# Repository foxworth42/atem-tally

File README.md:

# atem-tally
Yet another Arduino based ATEM tally light system.  This system is self-contained and talks to the ATEM directly.  The on camera lights are neo pixels driven over RS485 to allow for long cable runs.  The cabling between the cameras is done using ethernet cables for simplicity of wiring so we can send power + data to the remote lights.  The tally controller will also have a 20x4 LCD display for showing system status.  An XBee can also be added for supporting wireless remote tally lights.

# Still a work-in-progress

Everything here is still a work in process at the moment.  

Arduino code makes use of [Skaarhoj's Open Engineering arduino libraries](https://github.com/kasperskaarhoj/SKAARHOJ-Open-Engineering/tree/master/ArduinoLibs) for communicating with the Black Magic ATEM video switcher

Why roll something myself?  Cost, and it's an excuse to learn some C and do some PCB design.

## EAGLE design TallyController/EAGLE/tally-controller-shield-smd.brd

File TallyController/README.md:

Arduino based tally controller using the Arduino Mega w/ Ethernet.

Configuration of the tally controller is done via serial connection.  To configure send the following:

|Setting|Command|Note|
|---|---|---|
|Controller's IP|`Ix.x.x.x`|Replace x's with the controller's IP address|
|Controller's Netmask|`Nx.x.x.x`|Replace the x's with the controller's netmask|
|ATEM's IP|`Ax.x.x.x`|Replace the x's with the ATEM's IP address|
|Remote Camera #|`Rx`|Replace the x's with the camera # the wireless tally light is attached to|

Sample build of ATEM tally controller built in a parts organizer for portability for on-location use at conventions.

# BOM:

## Controller Board:

For `tally-controller-shield-smd.brd`

|Component|Quantity|Notes|Link|
|---|---|---|---|
|Controller Shield PCB|1|Can have board fabbed anywhere.|[Link](https://oshpark.com/shared_projects/vglxha97)|
|Freetronics EtherMEGA|1|Arduino Mega + Ethernet bundle.  I do not recommend using the Mega ETH from RobotDyn.|[Link](https://www.freetronics.com.au/products/ethermega-arduino-mega-2560-compatible-with-onboard-ethernet)|
|SN75174N RS485 Quad Line Driver|3| |[Link](https://www.mouser.com/ProductDetail/595-SN75174N)|
|LM2596 DC/DC buck converters|2|I used 1 for the main 5v for the project, and the other just for powering the Ethermega|[Link](https://www.amazon.com/dp/B06XZ1DKF2/ref=cm_sw_em_r_mt_dp_U_vQXREb0CJX45Z)|
|Molex 22-23-2021 2-pin header|4| |[Link](https://www.mouser.com/ProductDetail/538-22-23-2021)|
|Molex 22-23-2031 3-pin header|3| |[Link](https://www.mouser.com/ProductDetail/538-22-23-2031)|
|Molex 22-23-2041 4-pin header|2| |[Link](https://www.mouser.com/ProductDetail/538-22-23-2041)|
|Molex 22-23-2081 8-pin header|3| |[Link](https://www.mouser.com/ProductDetail/538-22-23-2081)|
|470ohm 0805 SMD resistor|1| | |
|10kohm 0805 SMD resistor|1| | |
|4.7kohm 0805 SMD resistor|1| | |
|120ohm 0805 SMD resistor|12| | |
|0.1uf 0805 SMD ceramic capacitor|3| | |
|10kohm potentiometer|2| |[Link](https://www.mouser.com/ProductDetail/858-P231-QC15BR10K)|
|1kohm potentiometer|1| | |
|Potentiometer knob|3| |[Red](https://www.mouser.com/ProductDetail/450-3021), [Green](https://www.mouser.com/ProductDetail/450-3024), [Blue](https://www.mouser.com/ProductDetail/450-3023), [Yellow](https://www.mouser.com/ProductDetail/450-3022)
|SPST Toggle Swithch|1| | |
|Mean Well RS-25-12 Power Supply|1| |[Link](https://www.mouser.com/ProductDetail/709-RS25-12)|
|Sparkfun XBee regulated breakout|1|Optional|[Link](https://www.mouser.com/ProductDetail/474-WRL-11373)|
|XBee Pro Transciever|1|Optional|[Link](https://www.mouser.com/ProductDetail/888-XB3-24Z8ST)|
|Dome atenna for Xbee|1|Optional|[Link](https://www.mouser.com/ProductDetail/712-ANT-DB1-WRT-RPS)|
|20x4 LCD i2c Display|1|Can be had cheap off ebay| |

## Camera output board:

For `RJ45 4ch Outout.brd`

Quantities noted here are for each output board.  Multiply as needed for multiple boards.

|Component|Quantity|Notes|Link|
|---|---|---|---|
|Output PCB|1|Oshpark minimum order is 3|[Link](https://oshpark.com/shared_projects/SH81yZph)|
|Amphenol RJHSE-5380-04|1|4-port RJ45 module|[Link](https://www.mouser.com/ProductDetail/523-RJHSE-5380-04)|
|Molex 22-23-2021 2-pin header|4|Only needed for CAM#DATA1 headers.  CAM#DATA2 is unused currently.|[Link](https://www.mouser.com/ProductDetail/538-22-23-2021)|

## Power distribution

For `Output Power Distro.brd`

Small board for distributing the 5v power to the controller shield, camera output boards

|Component|Quantity|Notes|Link|
|---|---|---|---|
|Power Distro PCB|1|Oshpark minimum order is 3|[Link](https://oshpark.com/shared_projects/CbdMb8Fg)|
|Molex 22-23-2021 2-pin header|6|Only needed for CAM#DATA1 headers.  CAM#DATA2 is unused currently.|[Link](https://www.mouser.com/ProductDetail/538-22-23-2021)|

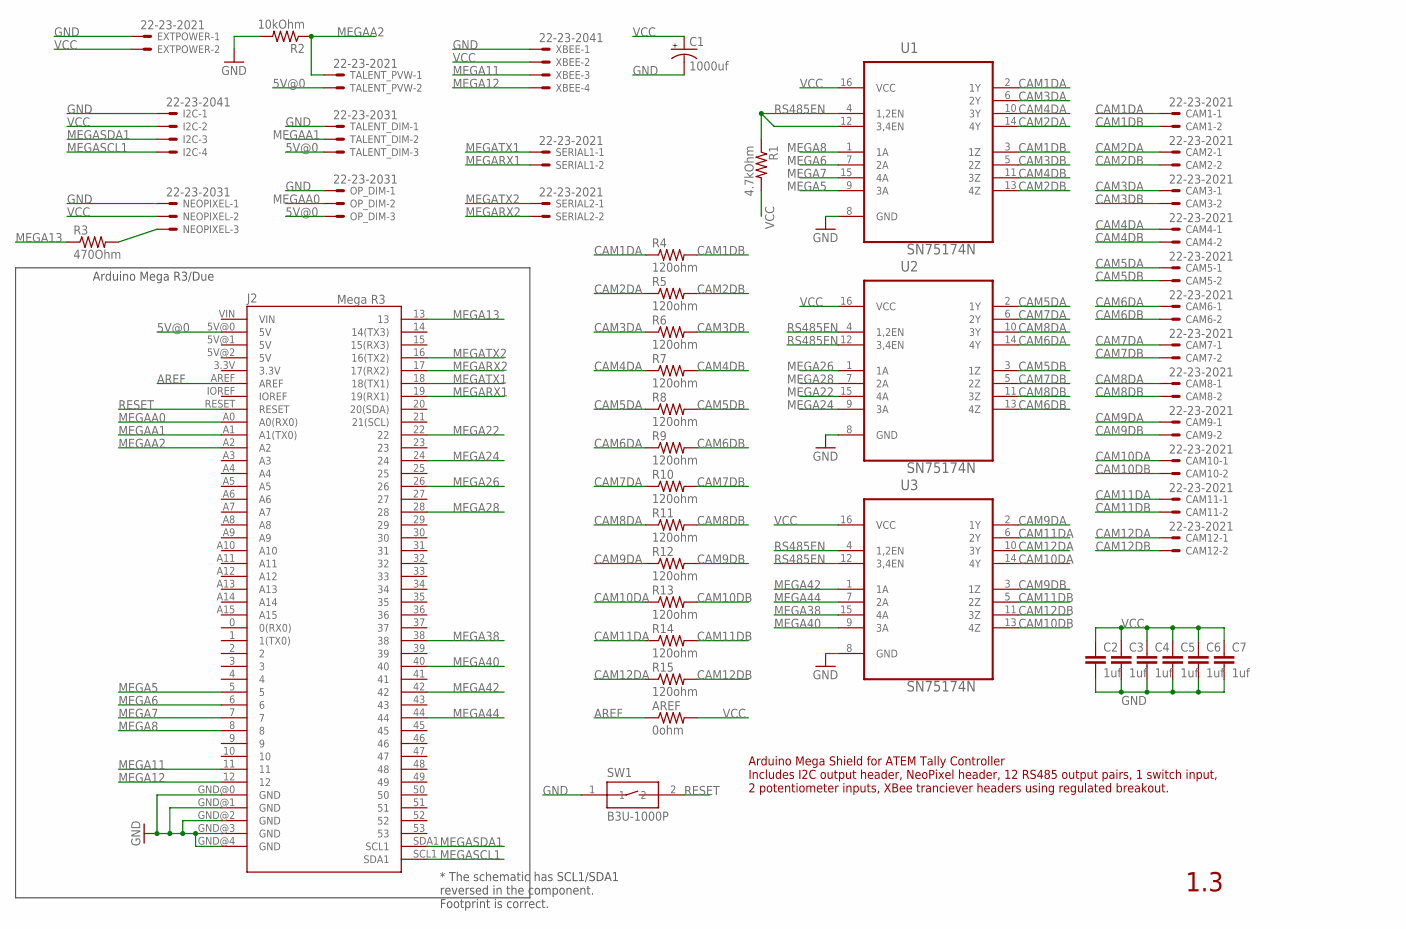
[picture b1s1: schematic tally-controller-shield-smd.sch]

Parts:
AREF: 0ohm; 0204V
C1: 1000uf; CPOL-RADIAL-5MM-10MM
C2, C3, C4, C5, C6, C7: 1uf; RESC0805_N
CAM1, CAM2, CAM3, CAM4, CAM5, CAM6, CAM7, CAM8, CAM9, CAM10, CAM11, CAM12: 22-23-2021
EXTPOWER: 22-23-2021
I2C: 22-23-2041
J2: Mega R3; ARDUINO_MEGA
NEOPIXEL: 22-23-2031
OP_DIM: 22-23-2031
R1: 4.7kOhm; R0805
R2: 10kOhm; R0805
R3: 470Ohm; R0805
R4, R5, R6, R7, R8, R9, R10, R11, R12, R13, R14, R15: 120ohm; R0805
SERIAL1, SERIAL2: 22-23-2021
SW1: B3U-1000P
TALENT_DIM: 22-23-2031
TALENT_PVW: 22-23-2021
U1, U2, U3: SN75174N; DIP254P762X508-16
XBEE: 22-23-2041

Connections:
5V@0: J2.5V@0 (5V), OP_DIM.3, TALENT_DIM.3, TALENT_PVW.2
AREF: AREF.1, J2.AREF
CAM1DA: CAM1.1, R4.1, U1.2 (1Y)
CAM1DB: CAM1.2, R4.2, U1.3 (1Z)
CAM2DA: CAM2.1, R5.1, U1.14 (4Y)
CAM2DB: CAM2.2, R5.2, U1.13 (4Z)
CAM3DA: CAM3.1, R6.1, U1.6 (2Y)
CAM3DB: CAM3.2, R6.2, U1.5 (2Z)
CAM4DA: CAM4.1, R7.1, U1.10 (3Y)
CAM4DB: CAM4.2, R7.2, U1.11 (3Z)
CAM5DA: CAM5.1, R8.1, U2.2 (1Y)
CAM5DB: CAM5.2, R8.2, U2.3 (1Z)
CAM6DA: CAM6.1, R9.1, U2.14 (4Y)
CAM6DB: CAM6.2, R9.2, U2.13 (4Z)
CAM7DA: CAM7.1, R10.1, U2.6 (2Y)
CAM7DB: CAM7.2, R10.2, U2.5 (2Z)
CAM8DA: CAM8.1, R11.1, U2.10 (3Y)
CAM8DB: CAM8.2, R11.2, U2.11 (3Z)
CAM9DA: CAM9.1, R12.1, U3.2 (1Y)
CAM9DB: CAM9.2, R12.2, U3.3 (1Z)
CAM10DA: CAM10.1, R13.1, U3.14 (4Y)
CAM10DB: CAM10.2, R13.2, U3.13 (4Z)
CAM11DA: CAM11.1, R14.1, U3.6 (2Y)
CAM11DB: CAM11.2, R14.2, U3.5 (2Z)
CAM12DA: CAM12.1, R15.1, U3.10 (3Y)
CAM12DB: CAM12.2, R15.2, U3.11 (3Z)
GND: C1.-, C2.2, C3.2, C4.2, C5.2, C6.2, C7.2, EXTPOWER.1, I2C.1, J2.GND@0 (GND), J2.GND@1 (GND), J2.GND@2 (GND), J2.GND@3 (GND), J2.GND@4 (GND), NEOPIXEL.1, OP_DIM.1, R2.2, SW1.1, TALENT_DIM.1, U1.8 (GND), U2.8 (GND), U3.8 (GND), XBEE.1
MEGA5: J2.5, U1.9 (3A)
MEGA6: J2.6, U1.7 (2A)
MEGA7: J2.7, U1.15 (4A)
MEGA8: J2.8, U1.1 (1A)
MEGA11: J2.11, XBEE.3
MEGA12: J2.12, XBEE.4
MEGA13: J2.13, R3.1
MEGA22: J2.22, U2.15 (4A)
MEGA24: J2.24, U2.9 (3A)
MEGA26: J2.26, U2.1 (1A)
MEGA28: J2.28, U2.7 (2A)
MEGA38: J2.38, U3.15 (4A)
MEGA40: J2.40, U3.9 (3A)
MEGA42: J2.42, U3.1 (1A)
MEGA44: J2.44, U3.7 (2A)
MEGAA0: J2.A0 (A0(RX0)), OP_DIM.2
MEGAA1: J2.A1 (A1(TX0)), TALENT_DIM.2
MEGAA2: J2.A2, R2.1, TALENT_PVW.1
MEGARX1: J2.19 (19(RX1)), SERIAL1.2
MEGARX2: J2.17 (17(RX2)), SERIAL2.2
MEGASCL1: I2C.4, J2.SCL1 (SDA1)
MEGASDA1: I2C.3, J2.SDA1 (SCL1)
MEGATX1: J2.18 (18(TX1)), SERIAL1.1
MEGATX2: J2.16 (16(TX2)), SERIAL2.1
NEOPIXELDATA: NEOPIXEL.3, R3.2
RESET: J2.RESET, SW1.2
RS485EN: R1.1, U1.4 (1,2EN), U1.12 (3,4EN), U2.4 (1,2EN), U2.12 (3,4EN), U3.4 (1,2EN), U3.12 (3,4EN)
VCC: AREF.2, C1.+, C2.1, C3.1, C4.1, C5.1, C6.1, C7.1, EXTPOWER.2, I2C.2, NEOPIXEL.2, R1.2, U1.16 (VCC), U2.16 (VCC), U3.16 (VCC), XBEE.2

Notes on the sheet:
Arduino Mega R3/Due
Arduino Mega Shield for ATEM Tally Controller Includes I2C output header, NeoPixel header, 12 RS485 output pairs, 1 switch input, 2 potentiometer inputs, XBee tranciever headers using regulated breakout.
1.3
* The schematic has SCL1/SDA1 reversed in the component. Footprint is correct.

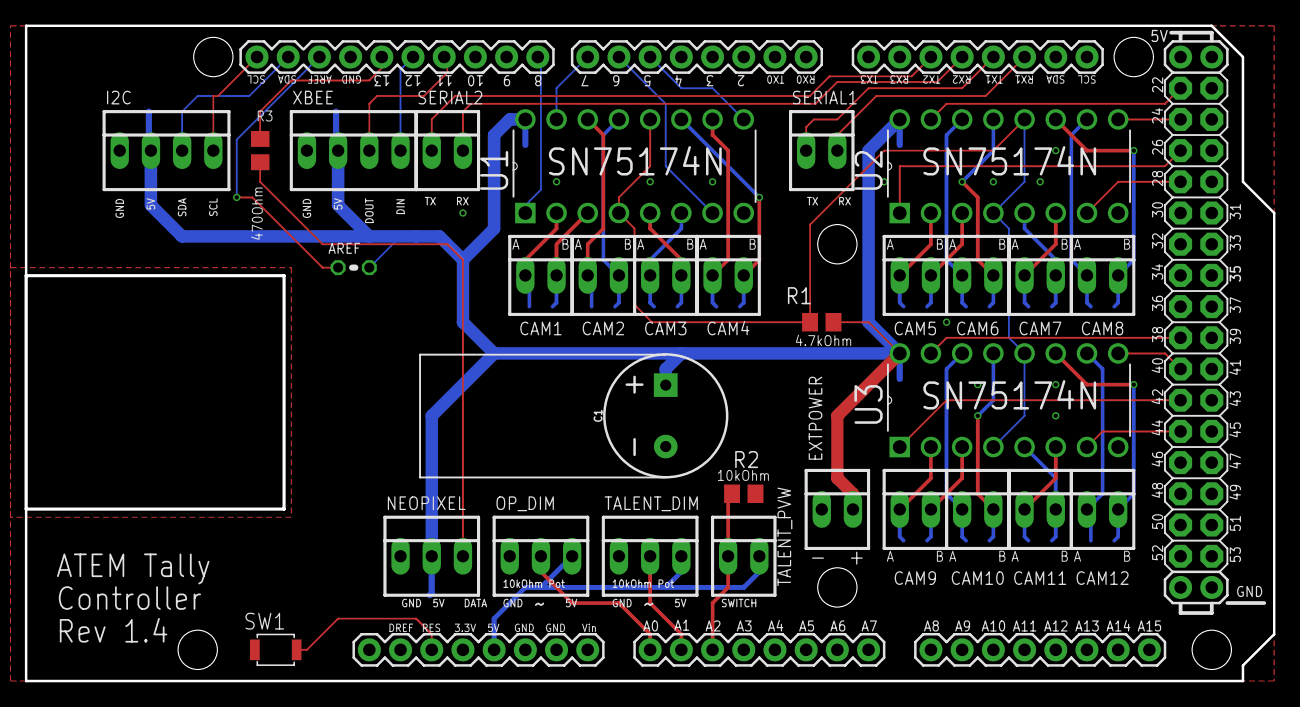
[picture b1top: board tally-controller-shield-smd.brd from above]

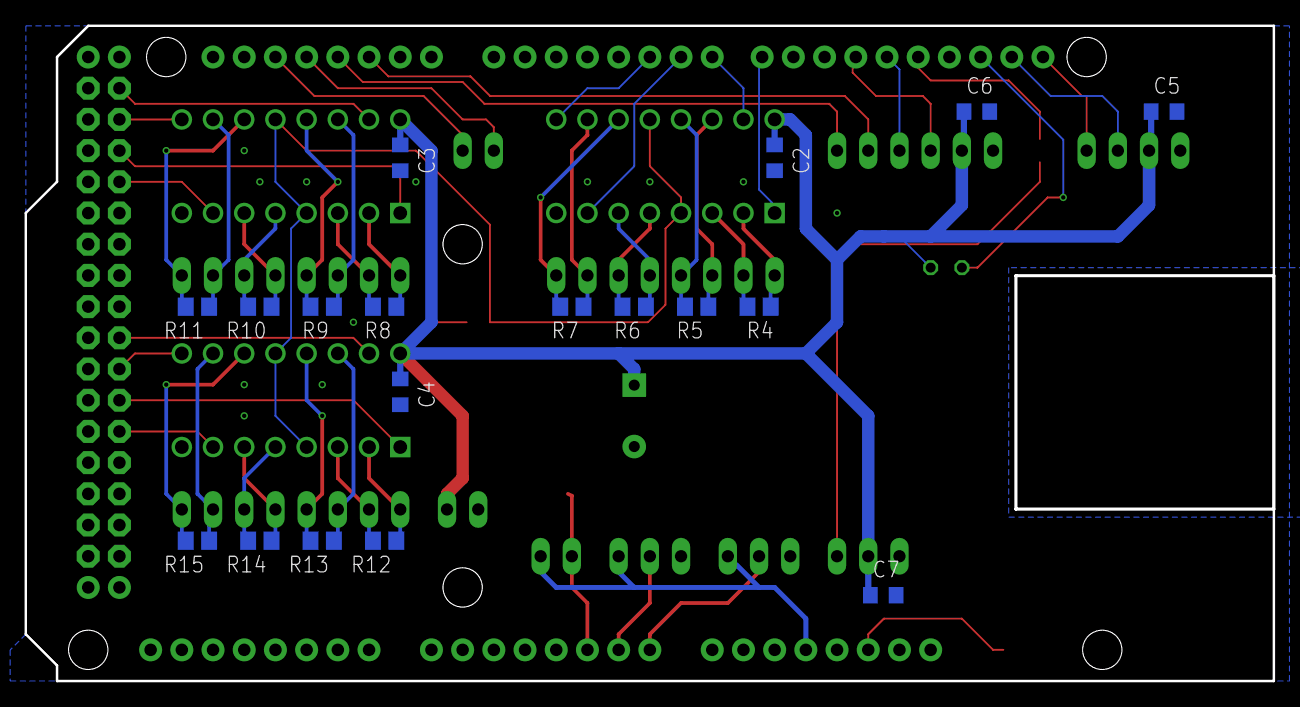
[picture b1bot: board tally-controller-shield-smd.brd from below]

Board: 2 copper layers, 101.6 x 53.3 mm, 49 parts (18 on the bottom side), 55 nets.

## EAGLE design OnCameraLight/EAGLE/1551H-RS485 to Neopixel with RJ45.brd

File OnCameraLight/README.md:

RS485 receiver to Neopixel adapter for on-camera light.

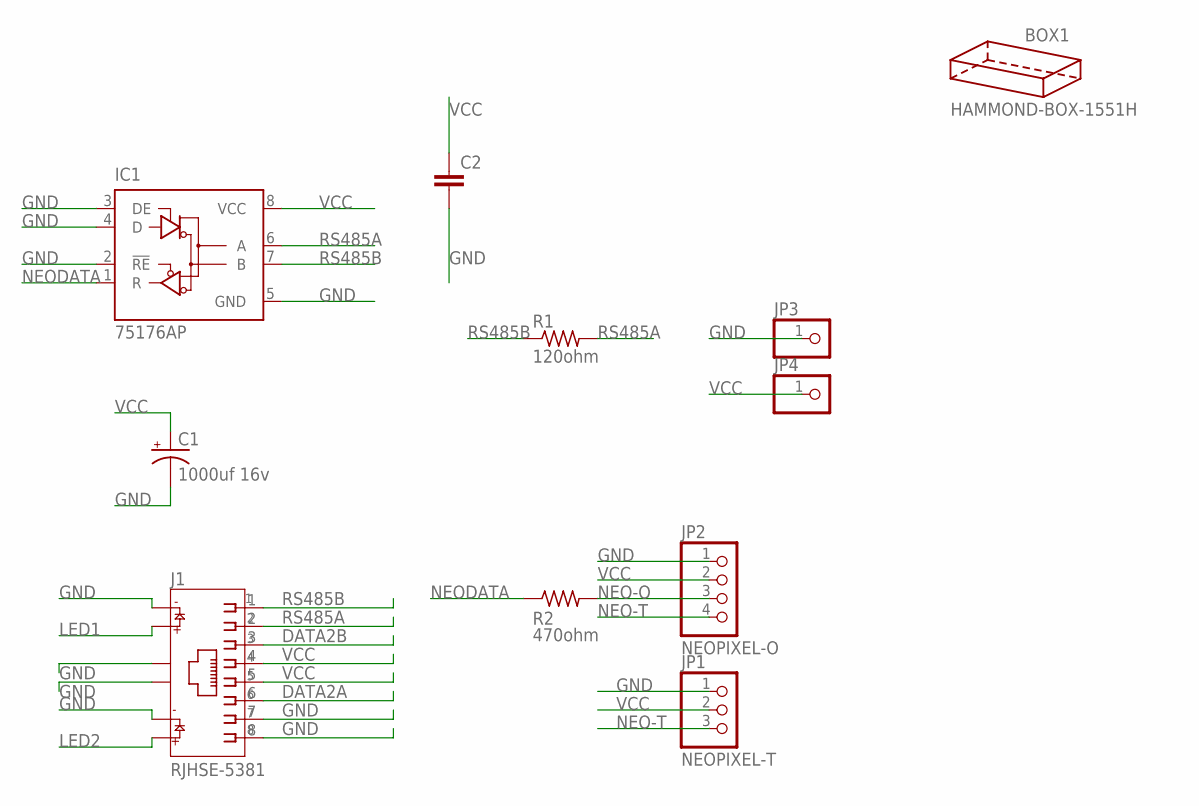
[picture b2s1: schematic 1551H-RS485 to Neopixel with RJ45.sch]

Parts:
BOX1: HAMMOND-BOX-1551H; 1551H
C1: 1000uf 16v; CPOL-RADIAL-5MM-10MM
C2: CAPACITOR_0805_N; RESC0805_N
IC1: 75176AP; DIL08
J1: RJHSE-5381; AMPHENOL_RJHSE-5381
JP1: NEOPIXEL-T; 1X03
JP2: NEOPIXEL-O; 1X04
JP3, JP4: PINHD-1X1; 1X01
R1: 120ohm; R0805
R2: 470ohm; R0805

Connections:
DATA2A: J1.6
DATA2B: J1.3
GND: C1.-, C2.2, IC1.2 (!RE), IC1.3 (DE), IC1.4 (D), IC1.5 (GND), J1.7, J1.8, J1.9, J1.11, J1.S1, J1.S2, JP1.1, JP2.1, JP3.1
LED1: J1.10
LED2: J1.12
NEO-O: JP2.3, R2.2
NEO-T: JP1.3, JP2.4
NEODATA: IC1.1 (R), R2.1
RS485A: IC1.6 (A), J1.2, R1.2
RS485B: IC1.7 (B), J1.1, R1.1
VCC: C1.+, C2.1, IC1.8 (VCC), J1.4, J1.5, JP1.2, JP2.2, JP4.1

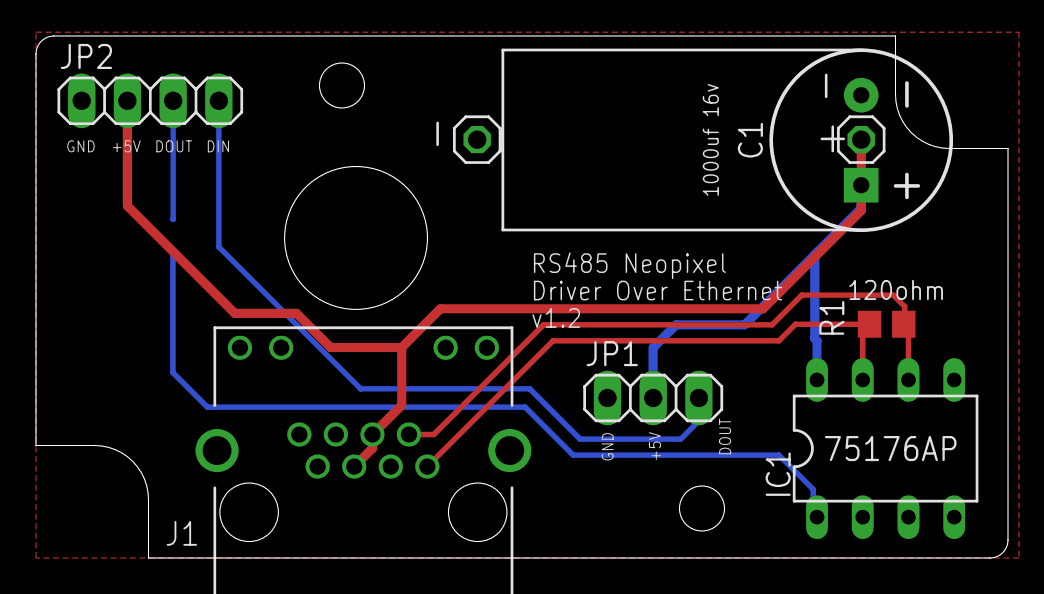
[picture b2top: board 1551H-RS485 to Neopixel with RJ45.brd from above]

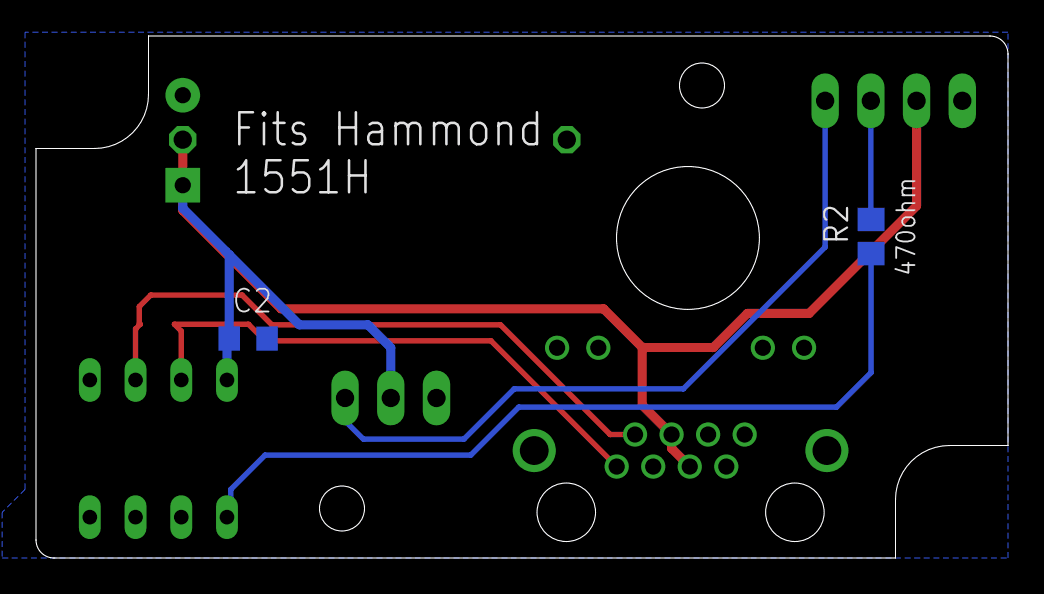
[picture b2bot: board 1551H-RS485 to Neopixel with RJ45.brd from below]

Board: 2 copper layers, 54.0 x 29.0 mm, 11 parts (2 on the bottom side), 7 nets.

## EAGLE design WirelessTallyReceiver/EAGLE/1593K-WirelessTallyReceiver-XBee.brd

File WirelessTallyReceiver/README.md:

XBee + Arduino Mini Pro based tally receiver.  Uses the same Neopixel LEDs as the wired lights, but wireless.

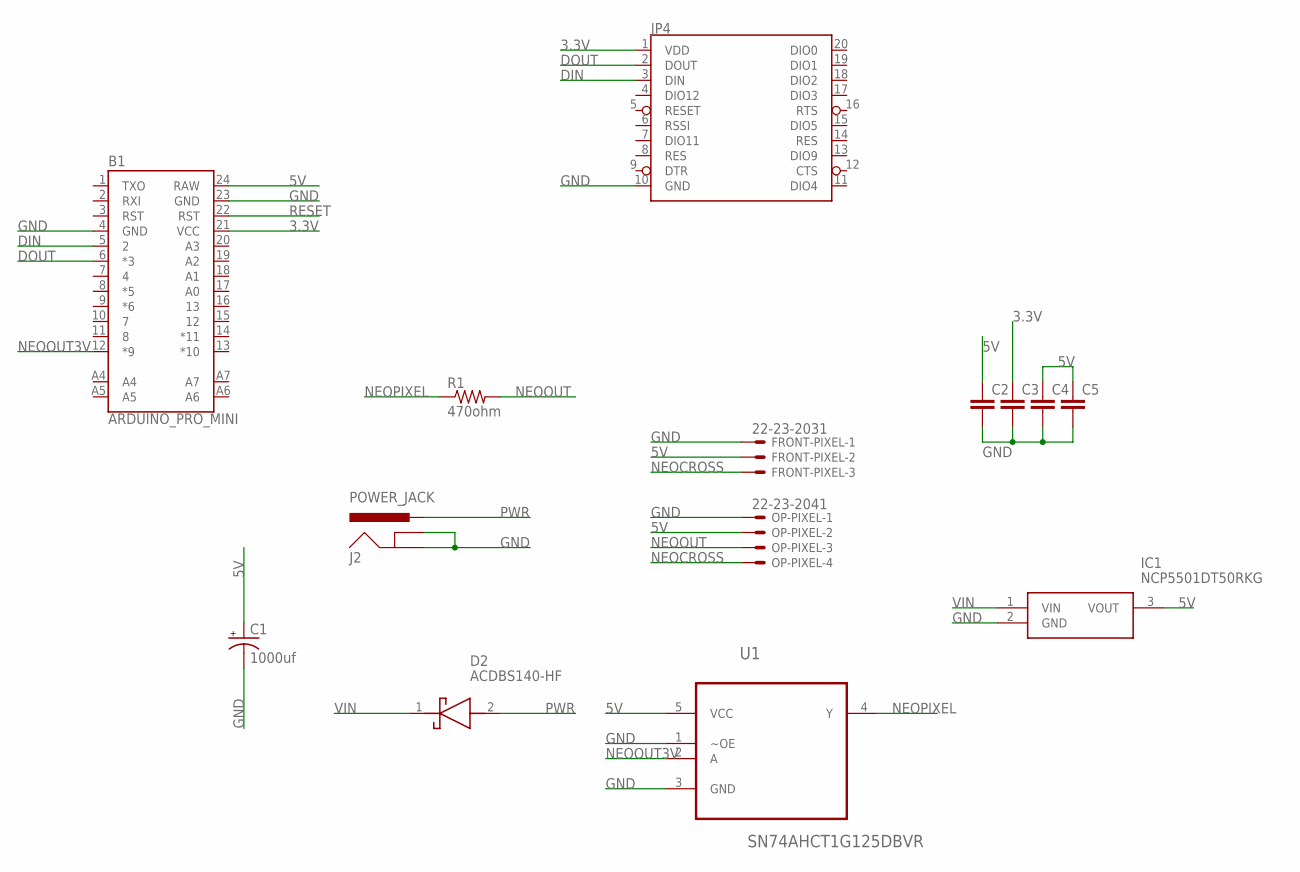
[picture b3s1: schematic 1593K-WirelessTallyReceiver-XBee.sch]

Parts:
B1: ARDUINO_PRO_MINI
C1: 1000uf; CPOL-RADIAL-5MM-10MM
C2, C3, C4, C5: CAPACITOR_0805_N; RESC0805_N
D2: ACDBS140-HF; DIOM2013X100N
FRONT-PIXEL: 22-23-2031
IC1: NCP5501DT50RKG
J2: POWER_JACK; POWER_JACK_PTH
JP4: XBEESILK; XBEE-SILK
OP-PIXEL: 22-23-2041
R1: 470ohm; R0805
U1: SN74AHCT1G125DBVR; SOT95P280X145-5N

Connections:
3.3V: B1.21 (VCC), C3.1, JP4.1 (VDD)
5V: B1.24 (RAW), C1.+, C2.1, C4.1, C5.1, FRONT-PIXEL.2, IC1.3 (VOUT), OP-PIXEL.2, U1.5 (VCC)
DIN: B1.5 (2), JP4.3 (DIN)
DOUT: B1.6 (*3), JP4.2 (DOUT)
GND: B1.4 (GND), B1.23 (GND), C1.-, C2.2, C3.2, C4.2, C5.2, FRONT-PIXEL.1, IC1.2 (GND), J2.GND, J2.GNDBREAK, JP4.10 (GND), OP-PIXEL.1, U1.1 (~OE), U1.3 (GND)
NEOCROSS: FRONT-PIXEL.3, OP-PIXEL.4
NEOOUT: OP-PIXEL.3, R1.2
NEOOUT3V: B1.12 (*9), U1.2 (A)
NEOPIXEL: R1.1, U1.4 (Y)
PWR: D2.2 (A), J2.PWR
RESET: B1.22 (RST)
VIN: D2.1 (K), IC1.1 (VIN)

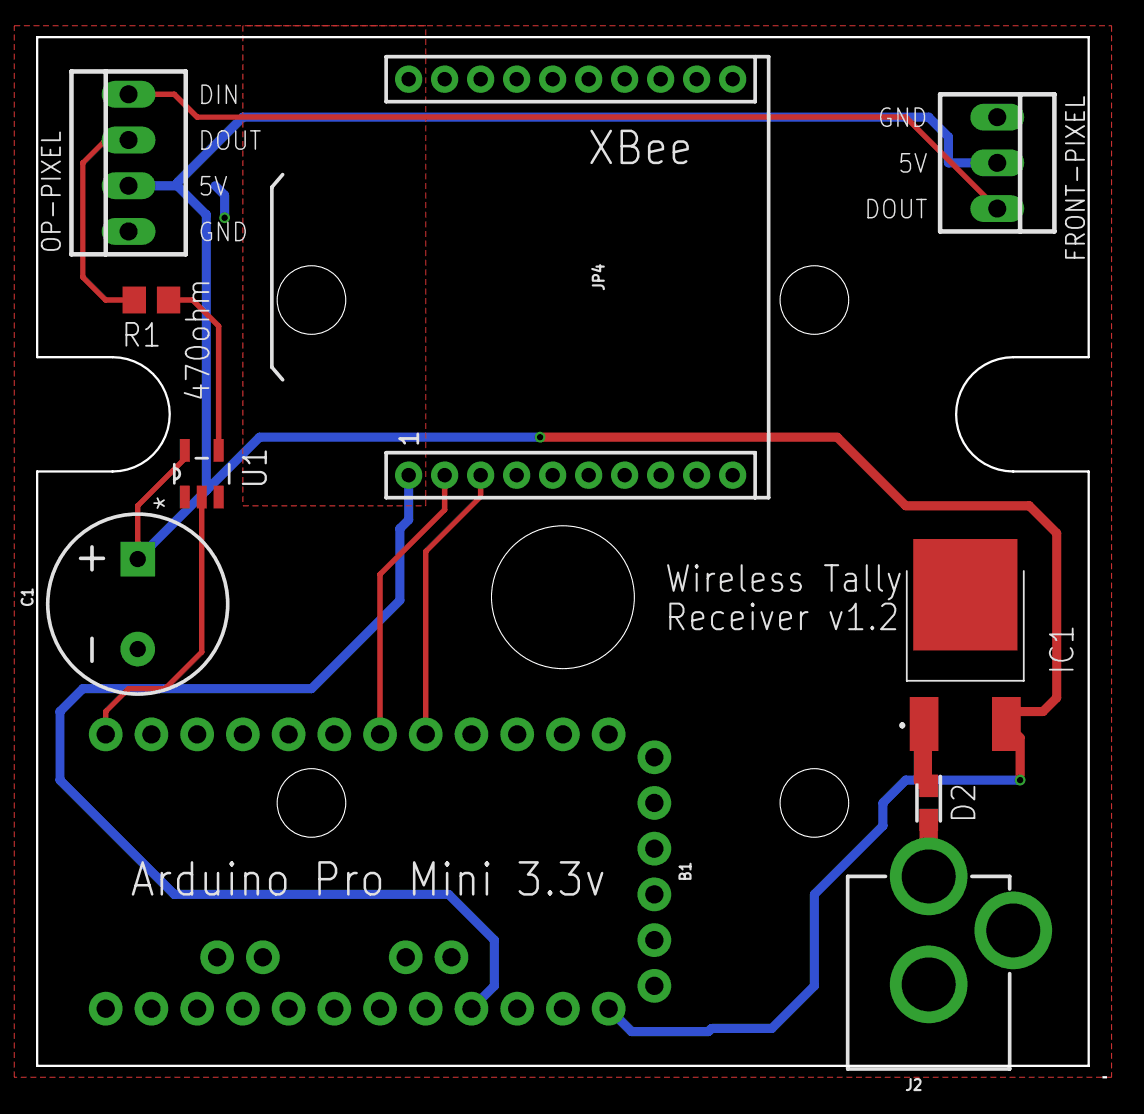
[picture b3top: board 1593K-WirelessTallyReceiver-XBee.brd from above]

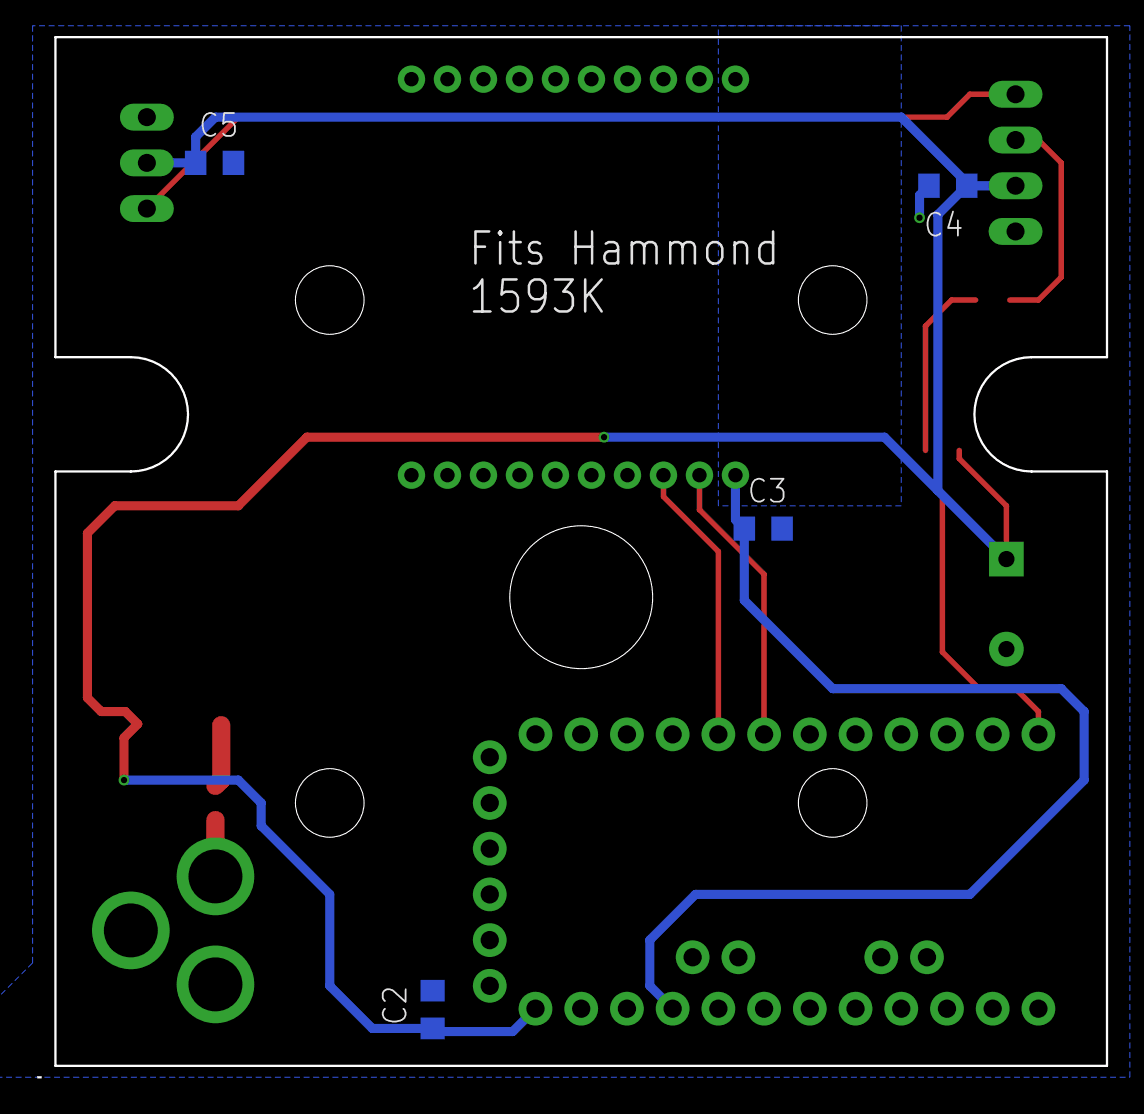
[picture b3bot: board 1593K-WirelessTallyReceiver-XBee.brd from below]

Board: 2 copper layers, 59.4 x 57.8 mm, 15 parts (4 on the bottom side), 11 nets.

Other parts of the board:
U$1: 1593K

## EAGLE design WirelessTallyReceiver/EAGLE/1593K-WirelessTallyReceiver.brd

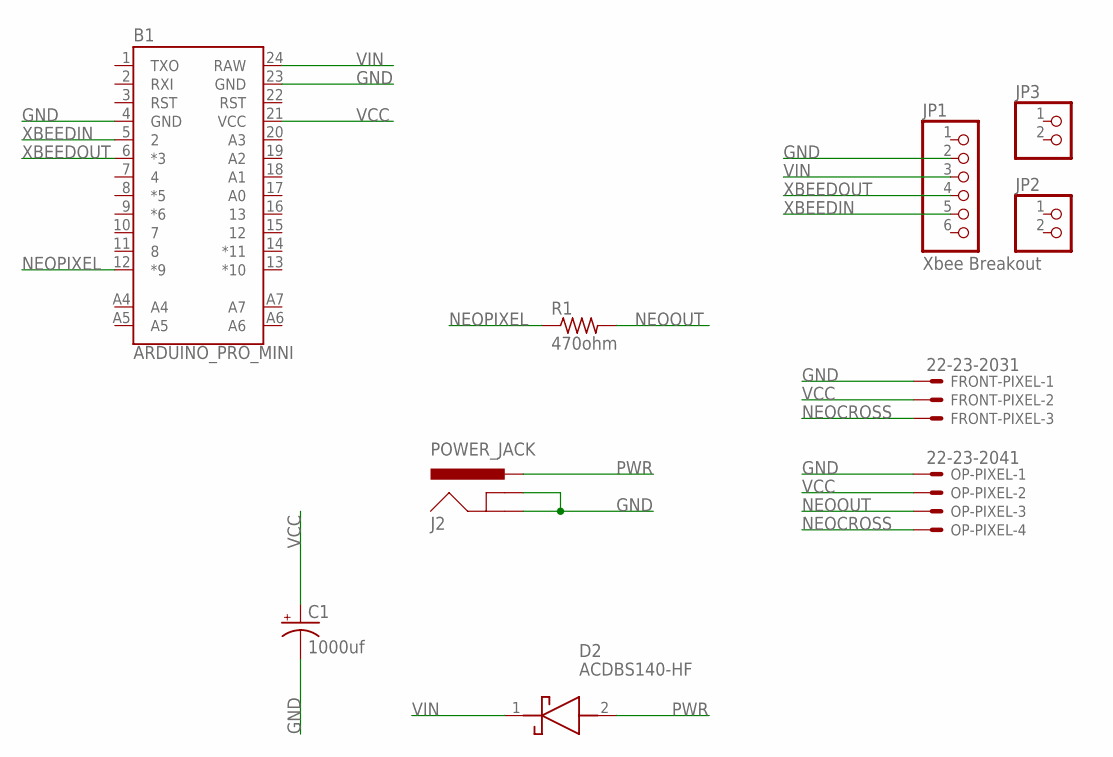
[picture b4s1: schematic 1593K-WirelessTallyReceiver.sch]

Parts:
B1: ARDUINO_PRO_MINI
C1: 1000uf; CPOL-RADIAL-5MM-10MM
D2: ACDBS140-HF; DIOM2013X100N
FRONT-PIXEL: 22-23-2031
J2: POWER_JACK; POWER_JACK_PTH
JP1: Xbee Breakout; 1X06
JP2, JP3: PINHD-1X2; 1X02
OP-PIXEL: 22-23-2041
R1: 470ohm; R0805

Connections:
GND: B1.4 (GND), B1.23 (GND), C1.-, FRONT-PIXEL.1, J2.GND, J2.GNDBREAK, JP1.2, OP-PIXEL.1
NEOCROSS: FRONT-PIXEL.3, OP-PIXEL.4
NEOOUT: OP-PIXEL.3, R1.2
NEOPIXEL: B1.12 (*9), R1.1
PWR: D2.2 (A), J2.PWR
VCC: B1.21 (VCC), C1.+, FRONT-PIXEL.2, OP-PIXEL.2
VIN: B1.24 (RAW), D2.1 (K), JP1.3
XBEEDIN: B1.5 (2), JP1.5
XBEEDOUT: B1.6 (*3), JP1.4

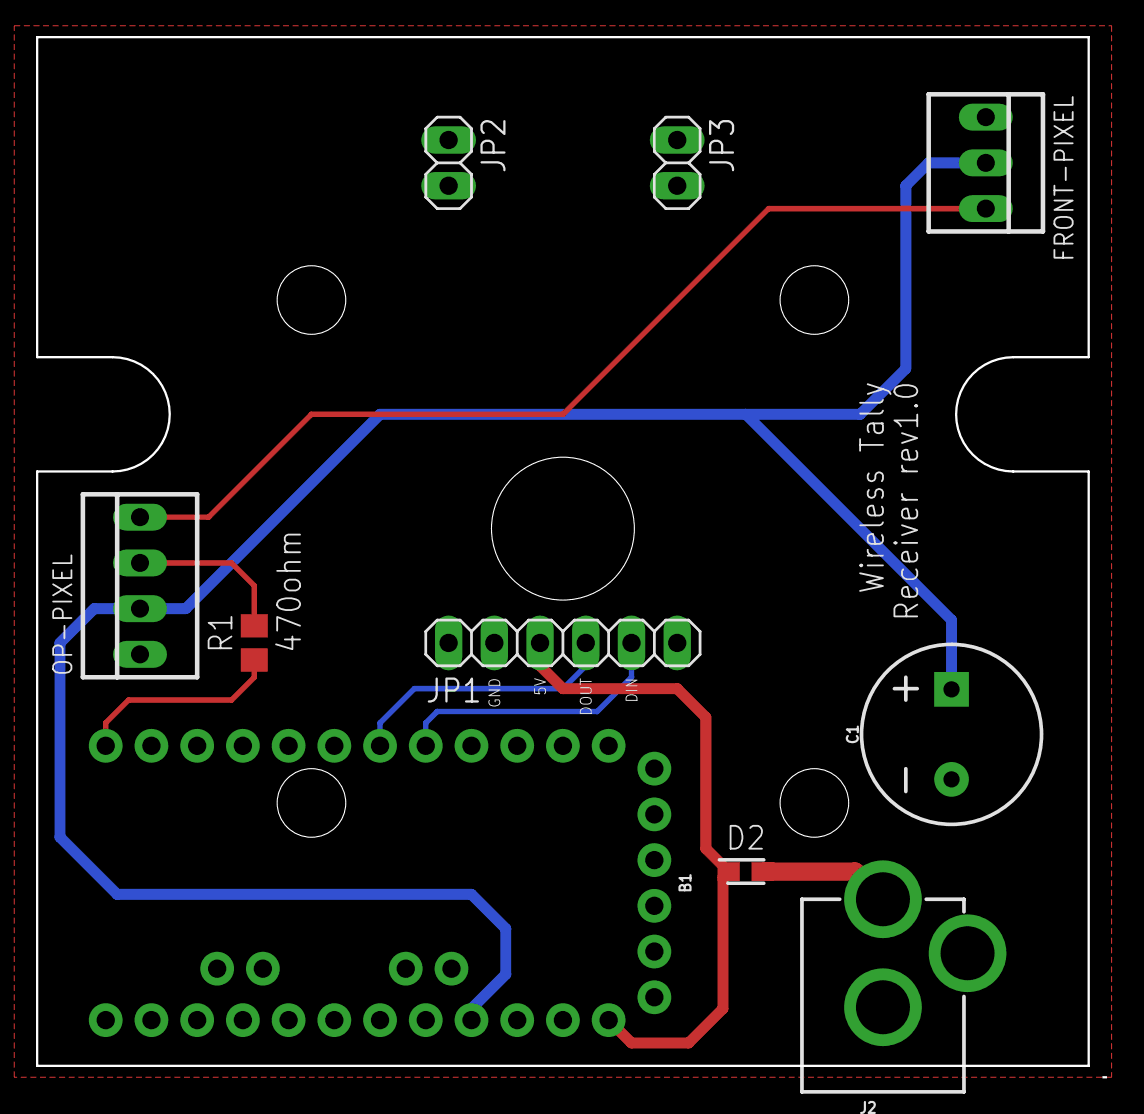
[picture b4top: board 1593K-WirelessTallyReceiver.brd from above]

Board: 2 copper layers, 59.4 x 57.8 mm, 11 parts (0 on the bottom side), 9 nets.

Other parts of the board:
U$1: 1593K

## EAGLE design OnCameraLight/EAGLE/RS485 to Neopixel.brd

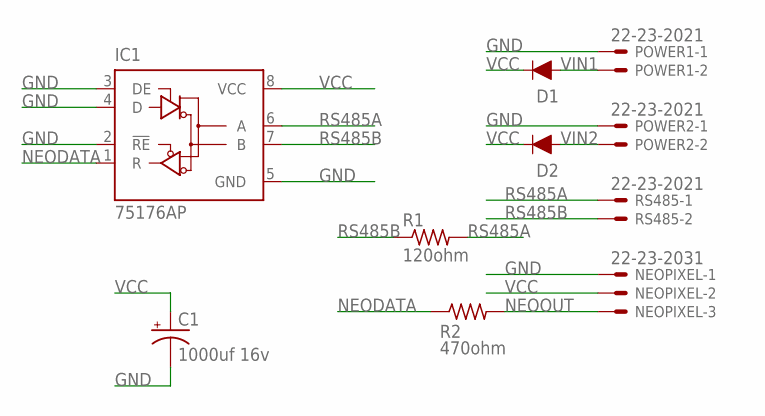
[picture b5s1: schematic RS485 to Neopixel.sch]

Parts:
C1: 1000uf 16v; CPOL-RADIAL-5MM-10MM
D1, D2: 1A/50V/1.1V; DIODE-1N4001
IC1: 75176AP; DIL08
NEOPIXEL: 22-23-2031
POWER1, POWER2: 22-23-2021
R1: 120ohm; 0207/10
R2: 470ohm; 0207/10
RS485: 22-23-2021

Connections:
GND: C1.-, IC1.2 (!RE), IC1.3 (DE), IC1.4 (D), IC1.5 (GND), NEOPIXEL.1, POWER1.1, POWER2.1
NEODATA: IC1.1 (R), R2.1
NEOOUT: NEOPIXEL.3, R2.2
RS485A: IC1.6 (A), R1.2, RS485.1
RS485B: IC1.7 (B), R1.1, RS485.2
VCC: C1.+, D1.C, D2.C, IC1.8 (VCC), NEOPIXEL.2
VIN1: D1.A, POWER1.2
VIN2: D2.A, POWER2.2

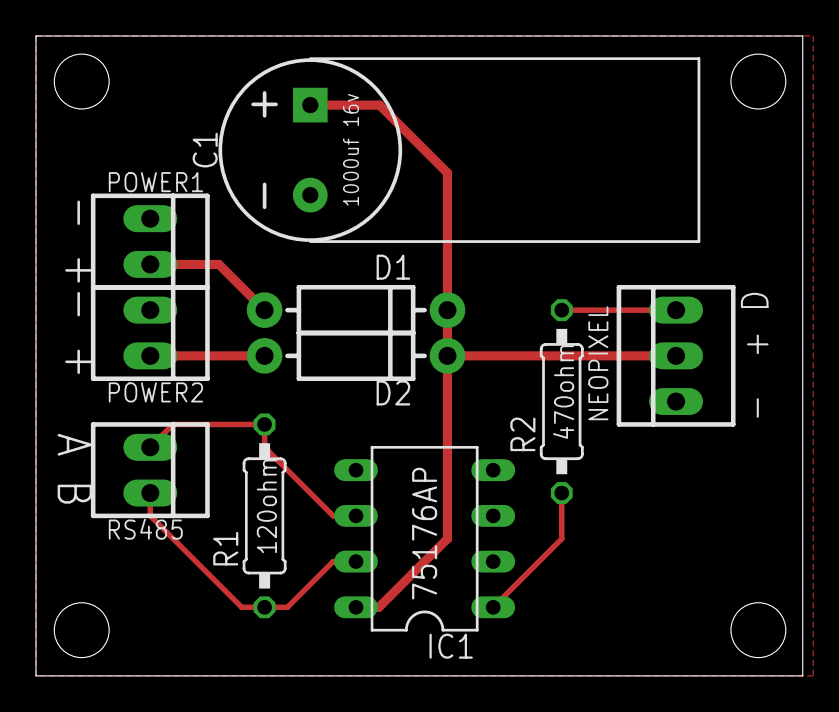
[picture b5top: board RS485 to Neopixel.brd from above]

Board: 2 copper layers, 42.6 x 35.5 mm, 10 parts (0 on the bottom side), 8 nets.

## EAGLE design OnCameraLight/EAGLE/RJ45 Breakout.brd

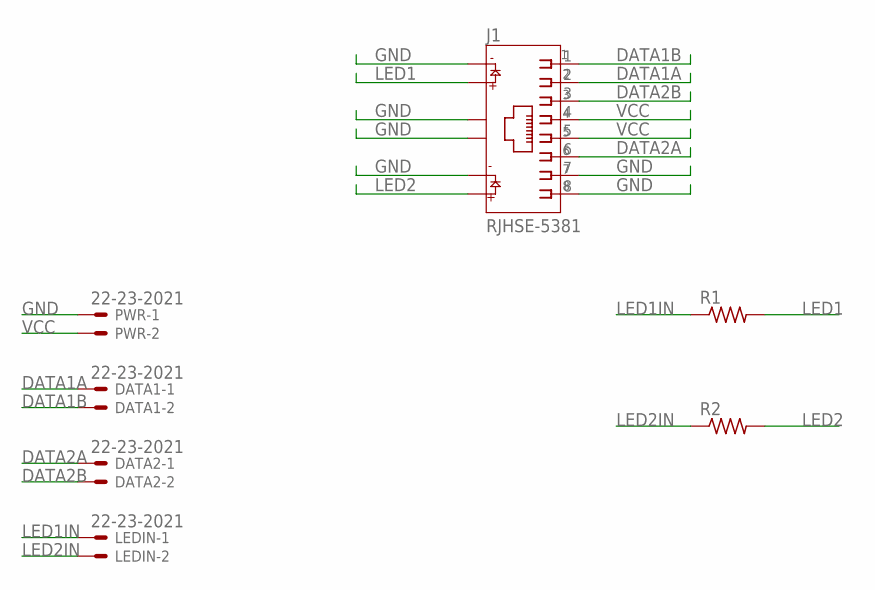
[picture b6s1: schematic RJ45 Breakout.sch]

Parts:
DATA1, DATA2: 22-23-2021
J1: RJHSE-5381; AMPHENOL_RJHSE-5381
LEDIN: 22-23-2021
PWR: 22-23-2021
R1, R2: R-US_0207/10; 0207/10

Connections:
DATA1A: DATA1.1, J1.2
DATA1B: DATA1.2, J1.1
DATA2A: DATA2.1, J1.6
DATA2B: DATA2.2, J1.3
GND: J1.7, J1.8, J1.9, J1.11, J1.S1, J1.S2, PWR.1
LED1: J1.10, R1.2
LED1IN: LEDIN.1, R1.1
LED2: J1.12, R2.2
LED2IN: LEDIN.2, R2.1
VCC: J1.4, J1.5, PWR.2

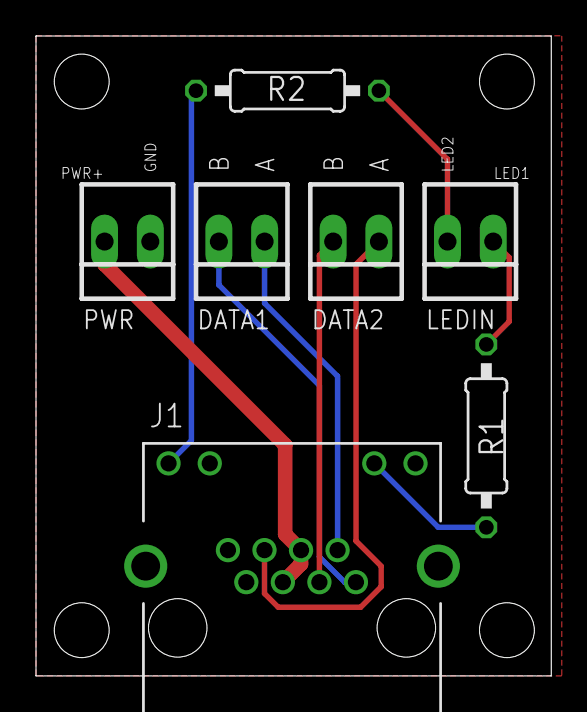
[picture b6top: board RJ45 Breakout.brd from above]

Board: 2 copper layers, 28.6 x 35.5 mm, 7 parts (0 on the bottom side), 10 nets.

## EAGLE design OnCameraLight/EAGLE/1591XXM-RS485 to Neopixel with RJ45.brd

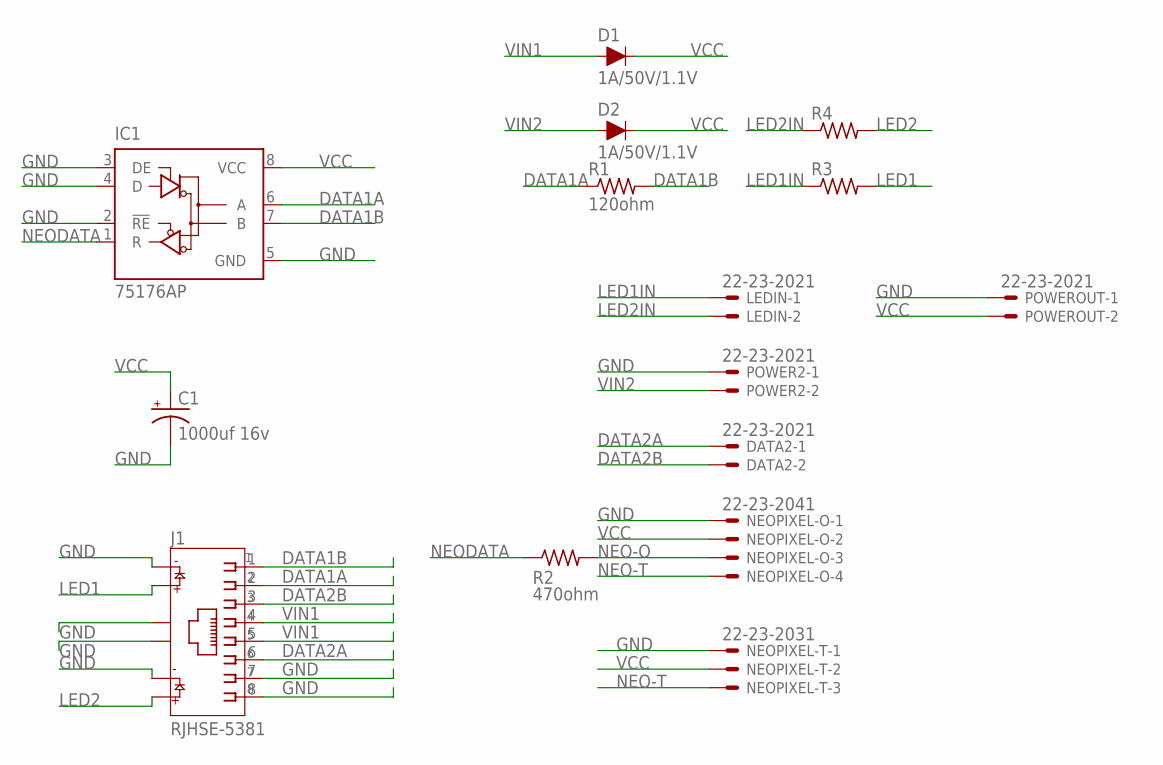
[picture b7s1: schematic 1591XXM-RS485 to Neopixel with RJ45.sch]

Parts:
C1: 1000uf 16v; CPOL-RADIAL-5MM-10MM
D1, D2: 1A/50V/1.1V; DIODE-1N4001
DATA2: 22-23-2021
IC1: 75176AP; DIL08
J1: RJHSE-5381; AMPHENOL_RJHSE-5381
LEDIN: 22-23-2021
NEOPIXEL-O: 22-23-2041
NEOPIXEL-T: 22-23-2031
POWER2: 22-23-2021
POWEROUT: 22-23-2021
R1: 120ohm; 0207/10
R2: 470ohm; 0207/10
R3, R4: R-US_0207/10; 0207/10

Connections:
DATA1A: IC1.6 (A), J1.2, R1.1
DATA1B: IC1.7 (B), J1.1, R1.2
DATA2A: DATA2.1, J1.6
DATA2B: DATA2.2, J1.3
GND: C1.-, IC1.2 (!RE), IC1.3 (DE), IC1.4 (D), IC1.5 (GND), J1.7, J1.8, J1.9, J1.11, J1.S1, J1.S2, NEOPIXEL-O.1, NEOPIXEL-T.1, POWER2.1, POWEROUT.1
LED1: J1.10, R3.2
LED1IN: LEDIN.1, R3.1
LED2: J1.12, R4.2
LED2IN: LEDIN.2, R4.1
NEO-O: NEOPIXEL-O.3, R2.2
NEO-T: NEOPIXEL-O.4, NEOPIXEL-T.3
NEODATA: IC1.1 (R), R2.1
VCC: C1.+, D1.C, D2.C, IC1.8 (VCC), NEOPIXEL-O.2, NEOPIXEL-T.2, POWEROUT.2
VIN1: D1.A, J1.4, J1.5
VIN2: D2.A, POWER2.2

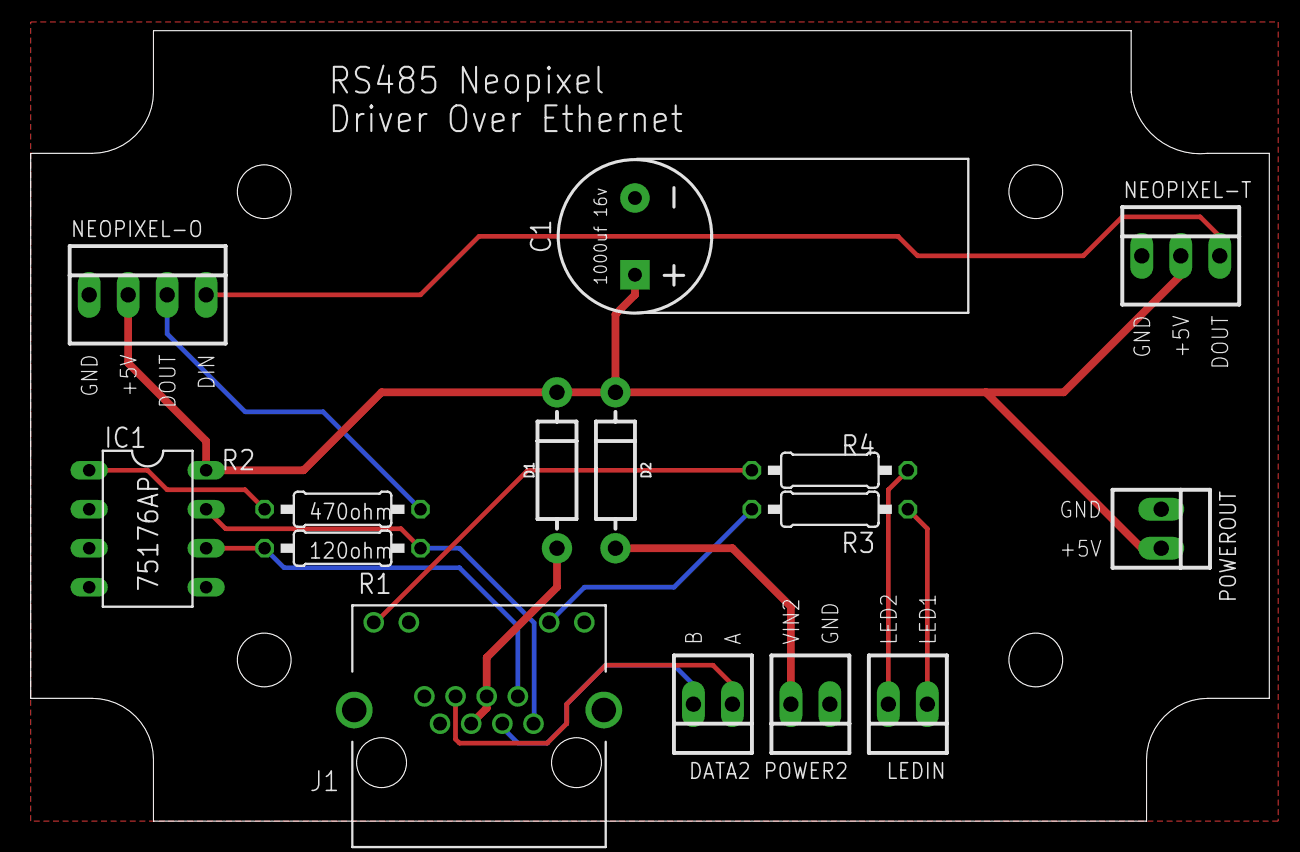
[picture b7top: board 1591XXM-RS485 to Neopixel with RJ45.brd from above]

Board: 2 copper layers, 80.7 x 51.5 mm, 16 parts (0 on the bottom side), 15 nets.

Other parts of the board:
U$1: 1591XXM

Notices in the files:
parts and their libraries:
SparkFun-Capacitors: Licensing: Creative Commons ShareAlike 4.0 International - https://creativecommons.org/licenses/by-sa/4.0
